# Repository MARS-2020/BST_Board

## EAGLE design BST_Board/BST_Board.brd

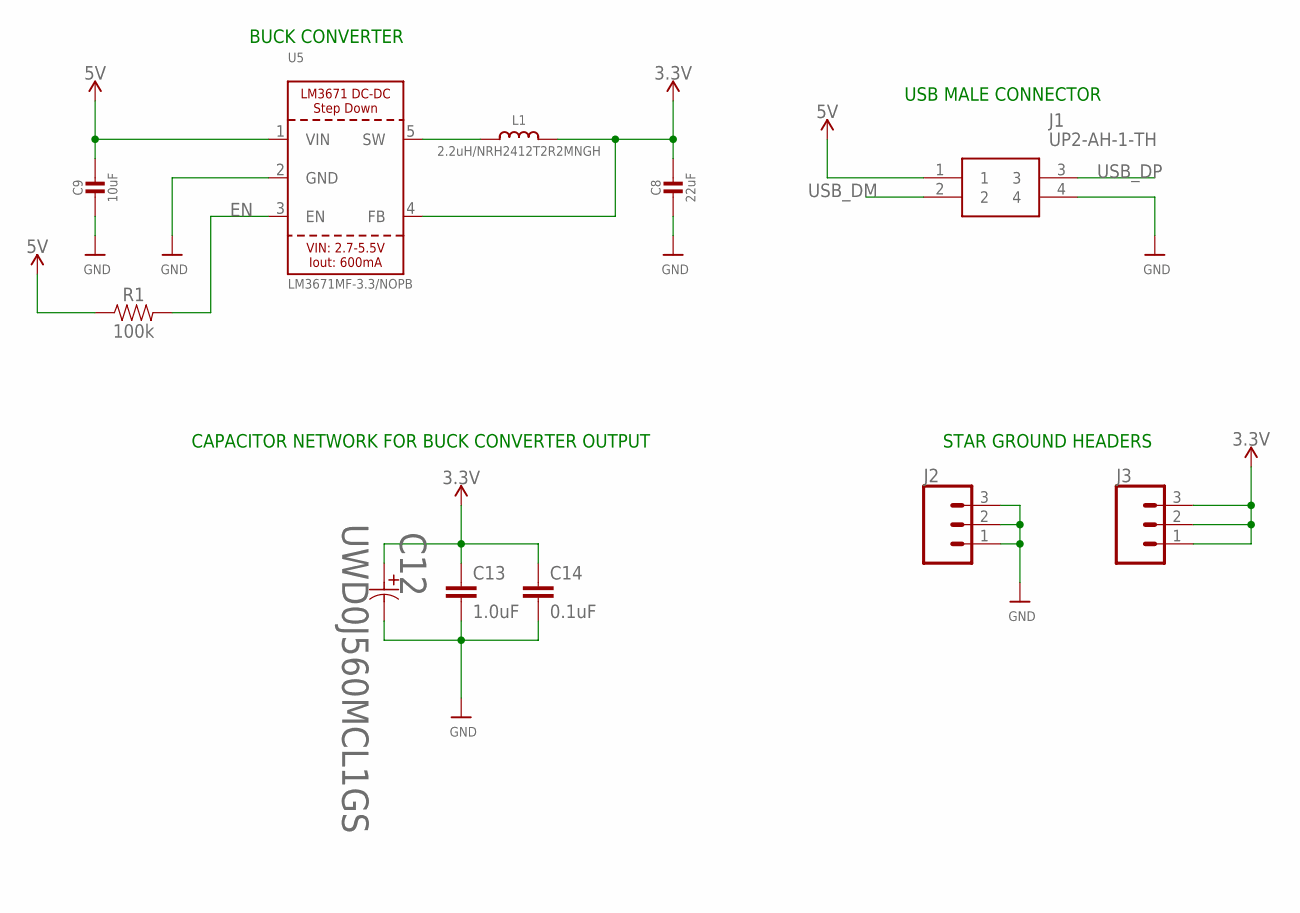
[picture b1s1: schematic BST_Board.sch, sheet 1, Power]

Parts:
C8: 22uF; 0805-NO
C9: 10uF; 0805-NO
C12: UWD0J560MCL1GS; PCAP_5X5.8-ELECT
C13: 1.0uF; 0603
C14: 0.1uF; 0603
J1: UP2-AH-1-TH
J2, J3: CONN_03; 1X03
L1: 2.2uH/NRH2412T2R2MNGH; INDUCTOR_TAIYOYUDEN_NRH2412T
R1: 100k; 0603
U5: LM3671MF-3.3/NOPB; SOT23-5

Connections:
3.3V: C8.1, C12.1, C13.1, C14.1, J3.1, J3.2, J3.3, L1.2, U5.4 (FB); also elsewhere on the board
5V: C9.1, J1.1, R1.1, U5.1 (VIN)
EN: R1.2, U5.3 (EN)
GND: C8.2, C9.2, C12.2, C13.2, C14.2, J1.4, J2.1, J2.2, J2.3, U5.2 (GND); also elsewhere on the board
unnamed: L1.1, U5.5 (SW)
USB_DM: J1.2; also elsewhere on the board
USB_DP: J1.3; also elsewhere on the board

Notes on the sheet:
BUCK CONVERTER
USB MALE CONNECTOR
CAPACITOR NETWORK FOR BUCK CONVERTER OUTPUT
STAR GROUND HEADERS

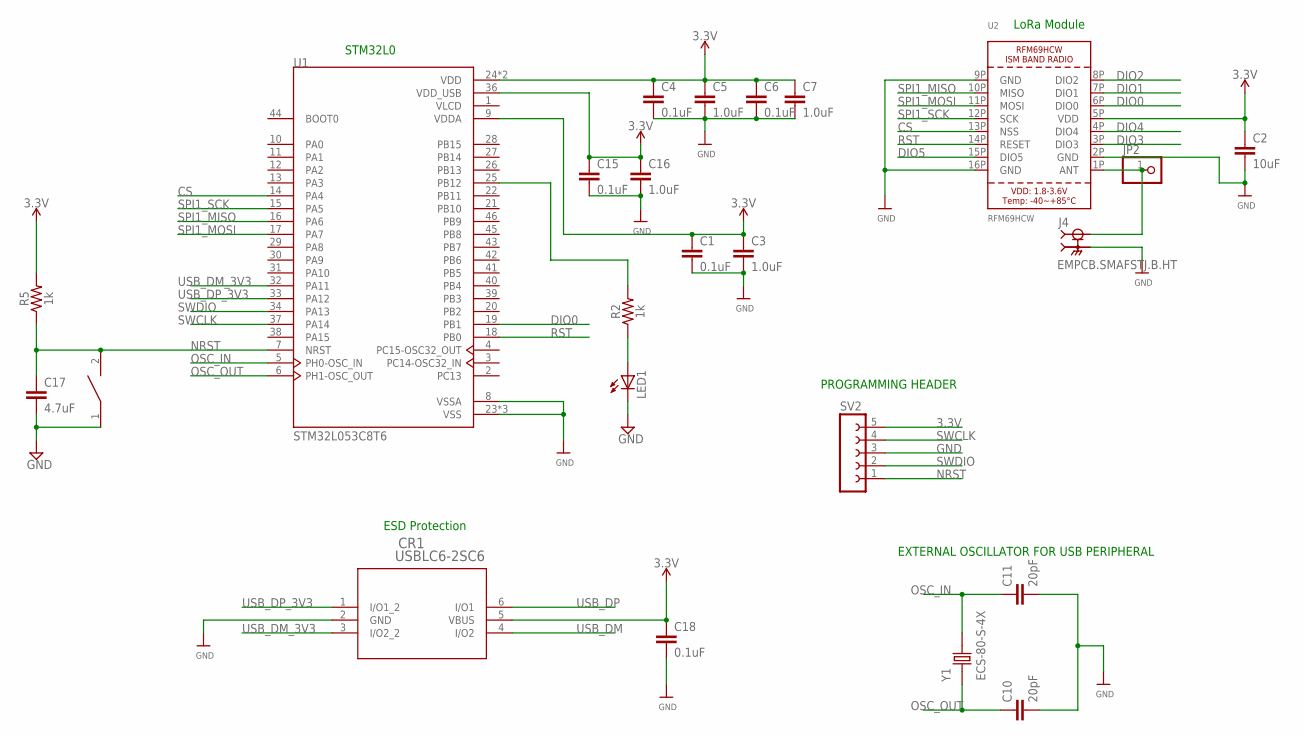
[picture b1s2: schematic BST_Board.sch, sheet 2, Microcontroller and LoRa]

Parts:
C1, C4, C6, C15, C18: 0.1uF; 0603
C2: 10uF; 0603
C3, C5, C7, C16: 1.0uF; 0603
C10, C11: 20pF; 0603
C17: 4.7uF; 0603
CR1: USBLC6-2SC6; SOT23-6L
J4: EMPCB.SMAFSTJ.B.HT; TAOGLAS_EMPCB.SMAFSTJ.B.HT
JP2: HEADER-1X1ROUND; 1X01_ROUND
LED1: LEDCHIP-LED0805; CHIP-LED0805
R2, R5: 1k; 0603
RESET: SWITCH; SW_2512
SV2: FE05-1
U1: STM32L053C8T6; QFP50P900X900X160-48N
U2: RFM69HCW; RFMHCW_SMT
Y1: ECS-80-S-4X; XTAL_ECS-80-S-4X

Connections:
3.3V: C1.1, C2.1, C3.1, C4.1, C5.1, C6.1, C7.1, C15.1, C16.1, C18.1, CR1.5 (VBUS), R5.2, SV2.5, U1.9 (VDDA), U1.24 (VDD), U1.36 (VDD_USB), U1.48 (VDD), U2.5P (VDD); also elsewhere on the board
CS: U1.14 (PA4), U2.13P (NSS)
DIO0: U1.19 (PB1), U2.6P (DIO0)
DIO1: U2.7P (DIO1)
DIO2: U2.8P (DIO2)
DIO3: U2.3P (DIO3)
DIO4: U2.4P (DIO4)
DIO5: U2.15P (DIO5)
GND: C1.2, C2.2, C3.2, C4.2, C5.2, C6.2, C7.2, C10.2, C11.2, C15.2, C16.2, C17.2, C18.2, CR1.2 (GND), J4.SH1 (2), J4.SH2 (2), J4.SH3 (2), J4.SH4 (2), LED1.C, RESET.1, SV2.3, U1.8 (VSSA), U1.23 (VSS), U1.35 (VSS), U1.44 (BOOT0), U1.47 (VSS), U2.2P (GND), U2.9P (GND), U2.16P (GND); also elsewhere on the board
unnamed: J4.1, JP2.1, U2.1P (ANT)
unnamed: R2.2, U1.25 (PB12)
unnamed: LED1.A, R2.1
NRST: C17.1, R5.1, RESET.2, SV2.1, U1.7 (NRST)
OSC_IN: C11.1, U1.5 (PH0-OSC_IN), Y1.2
OSC_OUT: C10.1, U1.6 (PH1-OSC_OUT), Y1.1
RST: U1.18 (PB0), U2.14P (RESET)
SPI1_MISO: U1.16 (PA6), U2.10P (MISO)
SPI1_MOSI: U1.17 (PA7), U2.11P (MOSI)
SPI1_SCK: U1.15 (PA5), U2.12P (SCK)
SWCLK: SV2.4, U1.37 (PA14)
SWDIO: SV2.2, U1.34 (PA13)
USB_DM: CR1.4 (I/O2); also elsewhere on the board
USB_DM_3V3: CR1.3 (I/O2_2), U1.32 (PA11)
USB_DP: CR1.6 (I/O1); also elsewhere on the board
USB_DP_3V3: CR1.1 (I/O1_2), U1.33 (PA12)

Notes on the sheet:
LoRa Module
EXTERNAL OSCILLATOR FOR USB PERIPHERAL
ESD Protection
PROGRAMMING HEADER
STM32L0

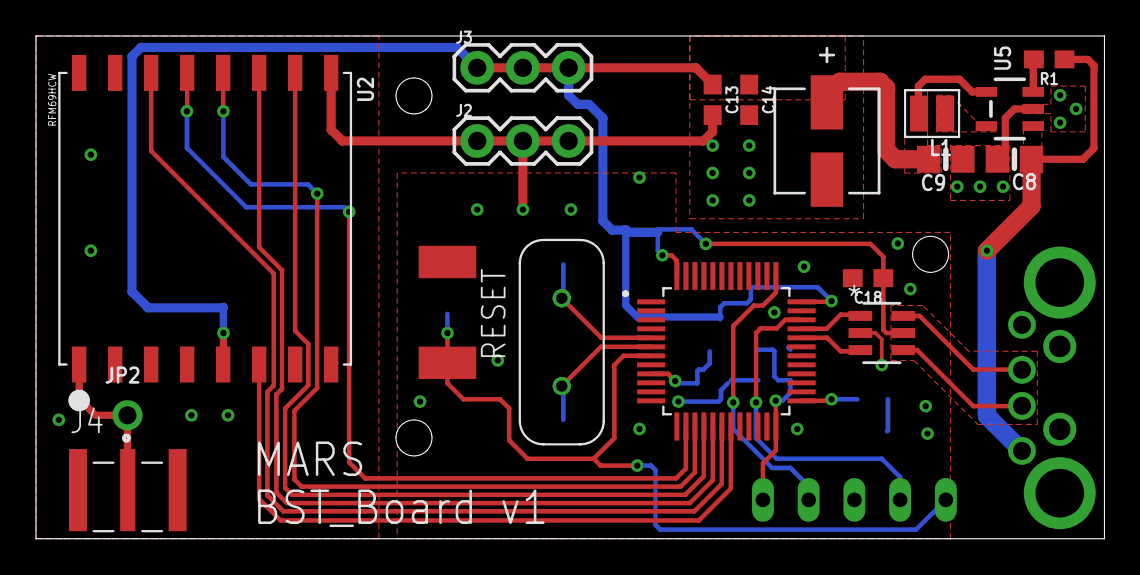
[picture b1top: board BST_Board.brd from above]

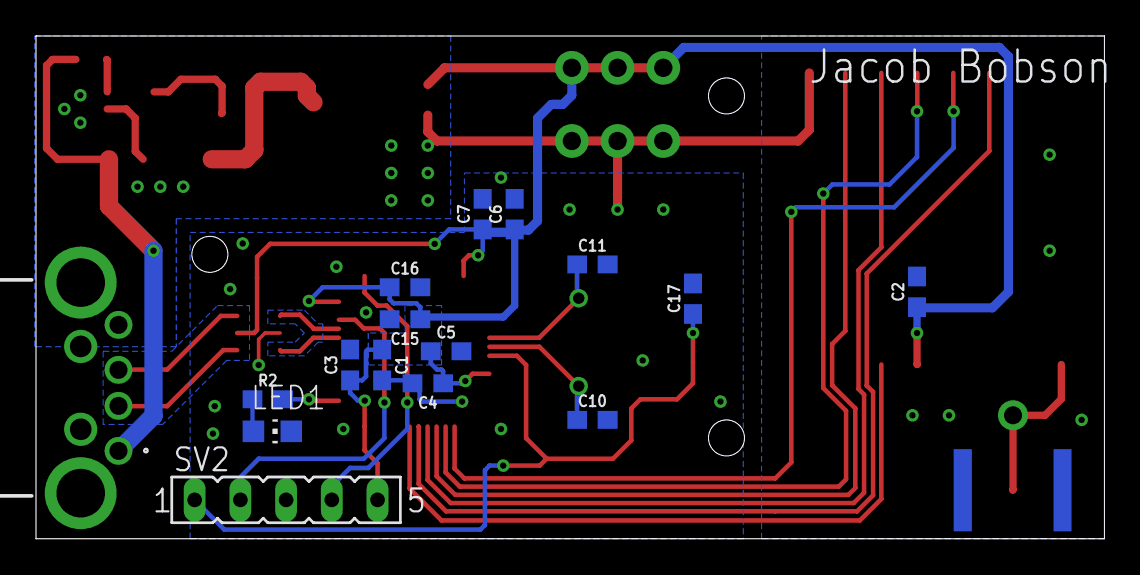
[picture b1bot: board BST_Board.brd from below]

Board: 2 copper layers, 59.4 x 27.9 mm, 34 parts (16 on the bottom side), 23 nets.

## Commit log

2020-01-28 Setup
2020-01-29 more shit
2020-01-29 More stuff added
2020-01-30 things and stuff
2020-01-31 Stuff
2020-02-03 Finished Initial Routing
2020-02-03 Added Labels
2020-02-03 GND Via
2020-02-04 Added Labels to Schematic
2020-02-11 renamed polygons
2020-02-11 LDO changes
2020-02-12 This board is a work of art
2020-02-12 added led indicator
2020-02-12 silkscreen
2020-02-12 mounting hole and feedback trace
2020-02-12 Final touches
2020-02-12 Label
2020-02-12 Renamed Files
2020-02-13 no clue what changed
2020-02-13 Not sure what changed
2020-02-18 Things
2020-02-26 Tied boot0 to ground
2020-02-26 Fixed reset circuit
2020-02-28 humm
2020-03-02 HMMMMMmmm

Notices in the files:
parts and their libraries:
microbuilder: This work is placed in the public domain, and may be freely used for commercial and non-commercial work with the following conditions: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
SparkFun-Capacitors: Licensing: Creative Commons ShareAlike 4.0 International - https://creativecommons.org/licenses/by-sa/4.0
